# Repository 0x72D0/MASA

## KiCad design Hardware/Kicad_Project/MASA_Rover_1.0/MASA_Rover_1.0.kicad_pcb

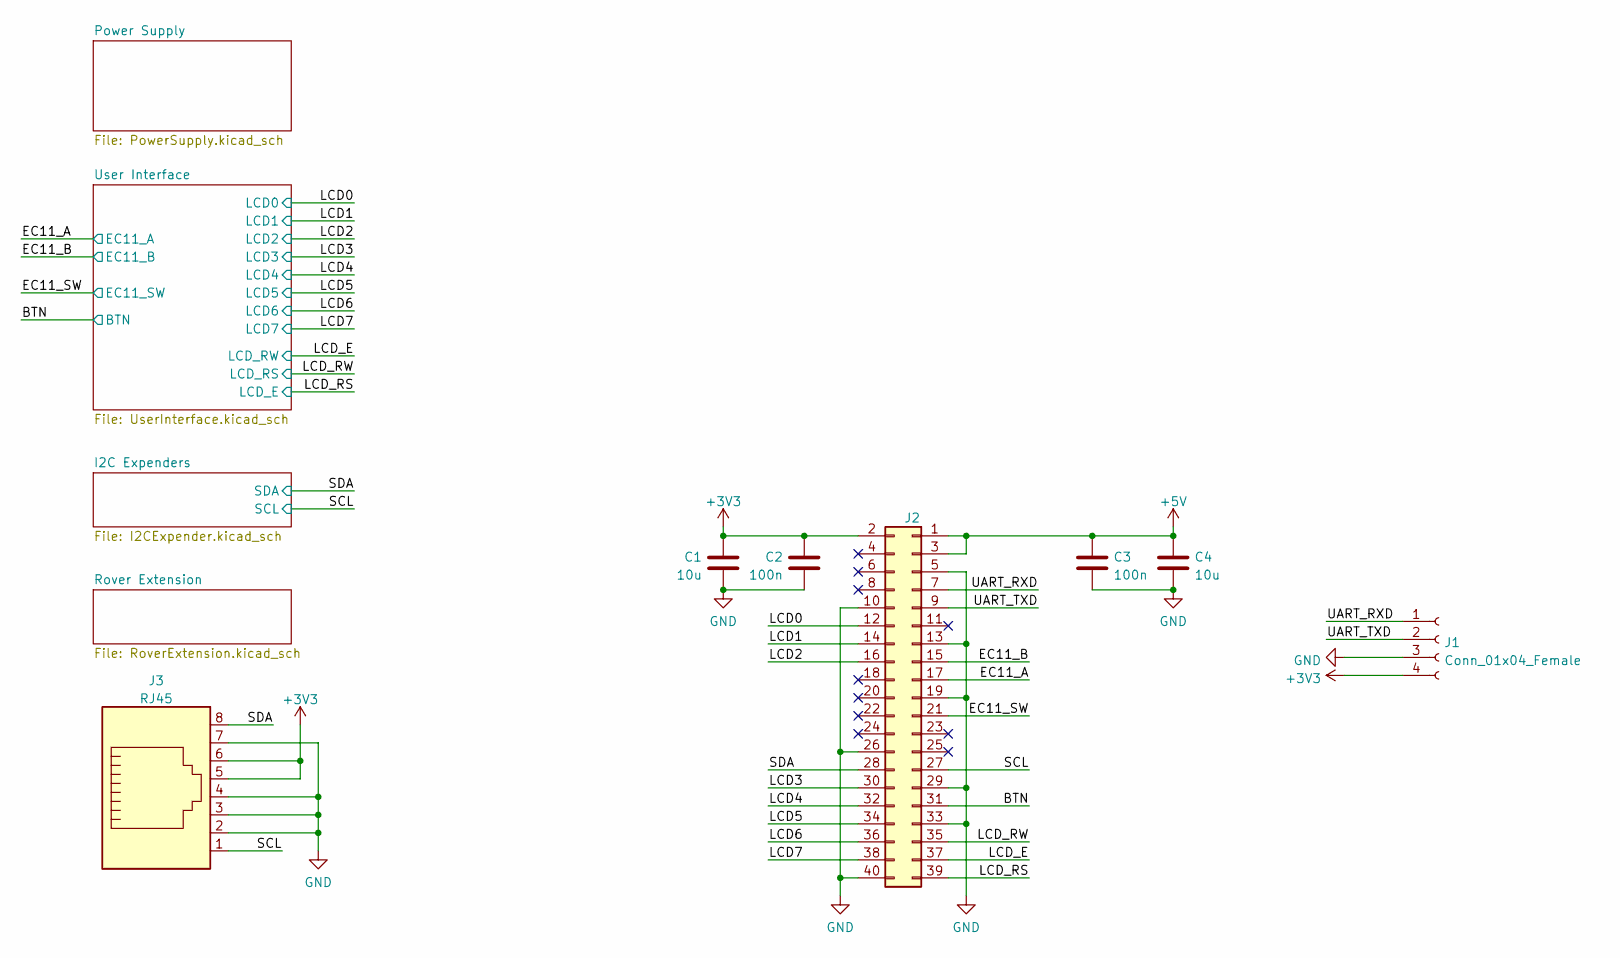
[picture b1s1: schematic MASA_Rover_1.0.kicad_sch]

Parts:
C1, C4: 10u; C_0805_2012Metric_Pad1.18x1.45mm_HandSolder
C2, C3: 100n; C_0805_2012Metric_Pad1.18x1.45mm_HandSolder
J1: Conn_01x04_Female; PinHeader_1x04_P2.54mm_Vertical
J2: Conn_02x20_Odd_Even; PinHeader_2x20_P2.54mm_Vertical
J3: RJ45; RJ45_Amphenol_54602-x08_Horizontal

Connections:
+3V3: C1.1, C2.1, J1.4, J2.2, J3.5, J3.6; also elsewhere on the board
+5V: C3.1, C4.1, J2.1, J2.3; also elsewhere on the board
/BTN: J2.31; also elsewhere on the board
/EC11_A: J2.17; also elsewhere on the board
/EC11_B: J2.15; also elsewhere on the board
/EC11_SW: J2.21; also elsewhere on the board
/LCD0: J2.12; also elsewhere on the board
/LCD1: J2.14; also elsewhere on the board
/LCD2: J2.16; also elsewhere on the board
/LCD3: J2.30; also elsewhere on the board
/LCD4: J2.32; also elsewhere on the board
/LCD5: J2.34; also elsewhere on the board
/LCD6: J2.36; also elsewhere on the board
/LCD7: J2.38; also elsewhere on the board
/LCD_E: J2.37; also elsewhere on the board
/LCD_RS: J2.39; also elsewhere on the board
/LCD_RW: J2.35; also elsewhere on the board
/SCL: J2.27, J3.1; also elsewhere on the board
/SDA: J2.28, J3.8; also elsewhere on the board
/UART_RXD: J1.1, J2.7
/UART_TXD: J1.2, J2.9
GND: C1.2, C2.2, C3.2, C4.2, J1.3, J2.5, J2.10, J2.13, J2.19, J2.26, J2.29, J2.33, J2.40, J3.2, J3.3, J3.4, J3.7; also elsewhere on the board

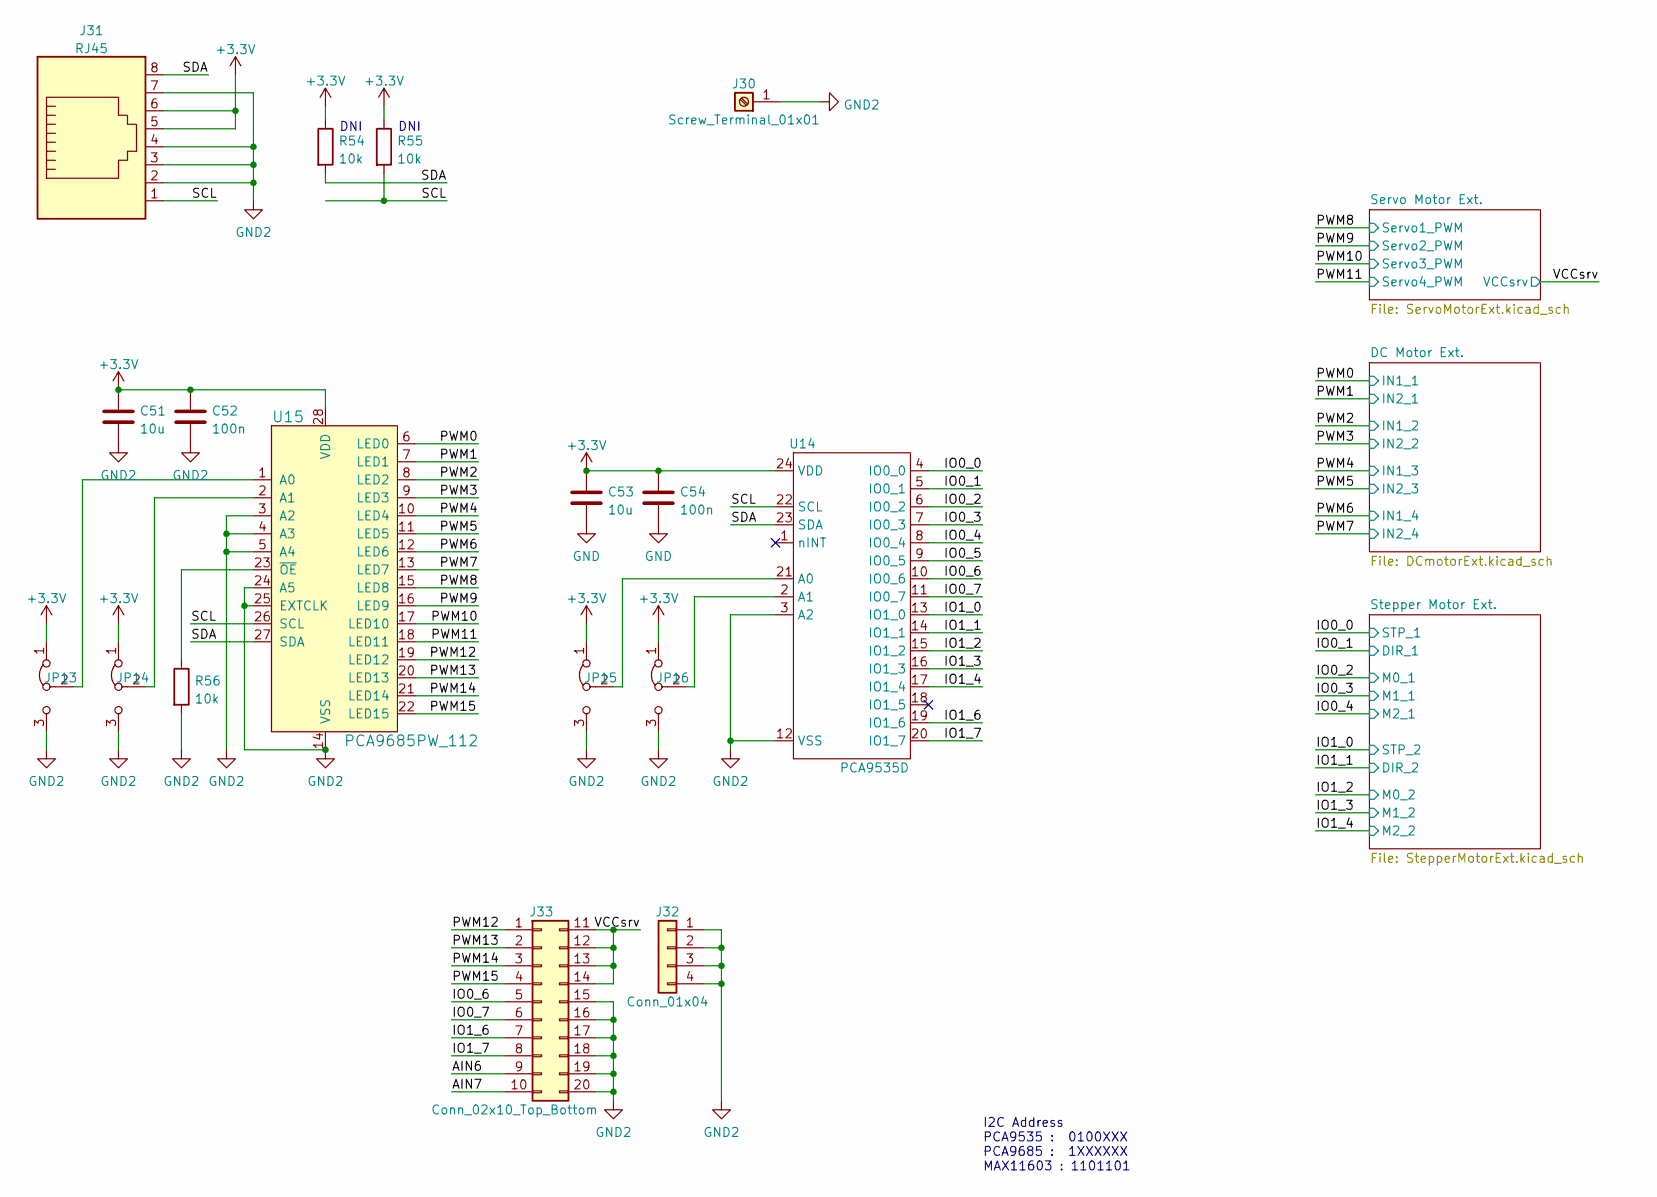
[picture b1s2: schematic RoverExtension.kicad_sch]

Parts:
C51, C53: 10u; C_0805_2012Metric_Pad1.18x1.45mm_HandSolder
C52, C54: 100n; C_0805_2012Metric_Pad1.18x1.45mm_HandSolder
J30: Screw_Terminal_01x01; ScrewTerminal_1x01_5x7mm
J31: RJ45; RJ45_Amphenol_54602-x08_Horizontal
J32: Conn_01x04; PinHeader_1x04_P2.54mm_Vertical
J33: Conn_02x10_Top_Bottom; PinHeader_2x10_P2.54mm_Vertical
JP13, JP14, JP15, JP16: Jumper_3_Bridged12; SolderJumper-3_P1.3mm_Bridged12_Pad1.0x1.5mm
R54, R55, R56: 10k; R_0805_2012Metric_Pad1.20x1.40mm_HandSolder
U14: PCA9535D; SOIC-24W_7.5x15.4mm_P1.27mm
U15: PCA9685PW_112; TSSOP-28_4.4x9.7mm_P0.65mm; MPN PCA9685PW,112; Digi-Key_PN 568-8366-5-ND

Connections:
+3.3V: C51.1, C52.1, C53.1, C54.1, J31.5, J31.6, JP13.1 (A), JP14.1 (A), JP15.1 (A), JP16.1 (A), R54.1, R55.1, U14.24 (VDD), U15.28 (VDD); also elsewhere on the board
/Rover Extension/AIN6: J33.9
/Rover Extension/AIN7: J33.10
/Rover Extension/IO0_0: U14.4 (IO0_0); also elsewhere on the board
/Rover Extension/IO0_1: U14.5 (IO0_1); also elsewhere on the board
/Rover Extension/IO0_2: U14.6 (IO0_2); also elsewhere on the board
/Rover Extension/IO0_3: U14.7 (IO0_3); also elsewhere on the board
/Rover Extension/IO0_4: U14.8 (IO0_4); also elsewhere on the board
/Rover Extension/IO0_5: U14.9 (IO0_5)
/Rover Extension/IO0_6: J33.5, U14.10 (IO0_6)
/Rover Extension/IO0_7: J33.6, U14.11 (IO0_7)
/Rover Extension/IO1_0: U14.13 (IO1_0); also elsewhere on the board
/Rover Extension/IO1_1: U14.14 (IO1_1); also elsewhere on the board
/Rover Extension/IO1_2: U14.15 (IO1_2); also elsewhere on the board
/Rover Extension/IO1_3: U14.16 (IO1_3); also elsewhere on the board
/Rover Extension/IO1_4: U14.17 (IO1_4); also elsewhere on the board
/Rover Extension/IO1_6: J33.7, U14.19 (IO1_6)
/Rover Extension/IO1_7: J33.8, U14.20 (IO1_7)
/Rover Extension/PWM0: U15.6 (LED0); also elsewhere on the board
/Rover Extension/PWM1: U15.7 (LED1); also elsewhere on the board
/Rover Extension/PWM2: U15.8 (LED2); also elsewhere on the board
/Rover Extension/PWM3: U15.9 (LED3); also elsewhere on the board
/Rover Extension/PWM4: U15.10 (LED4); also elsewhere on the board
/Rover Extension/PWM5: U15.11 (LED5); also elsewhere on the board
/Rover Extension/PWM6: U15.12 (LED6); also elsewhere on the board
/Rover Extension/PWM7: U15.13 (LED7); also elsewhere on the board
/Rover Extension/PWM8: U15.15 (LED8); also elsewhere on the board
/Rover Extension/PWM9: U15.16 (LED9); also elsewhere on the board
/Rover Extension/PWM10: U15.17 (LED10); also elsewhere on the board
/Rover Extension/PWM11: U15.18 (LED11); also elsewhere on the board
/Rover Extension/PWM12: J33.1, U15.19 (LED12)
/Rover Extension/PWM13: J33.2, U15.20 (LED13)
/Rover Extension/PWM14: J33.3, U15.21 (LED14)
/Rover Extension/PWM15: J33.4, U15.22 (LED15)
/Rover Extension/SCL: J31.1, R55.2, U14.22 (SCL), U15.26 (SCL)
/Rover Extension/SDA: J31.8, R54.2, U14.23 (SDA), U15.27 (SDA)
/Rover Extension/VCCsrv: J33.11, J33.12, J33.13, J33.14; also elsewhere on the board
GND: C53.2, C54.2; also elsewhere on the board
GND2: C51.2, C52.2, J30.1, J31.2, J31.3, J31.4, J31.7, J32.1, J32.2, J32.3, J32.4, J33.15, J33.16, J33.17, J33.18, J33.19, J33.20, JP13.3 (B), JP14.3 (B), JP15.3 (B), JP16.3 (B), R56.2, U14.3 (A2), U14.12 (VSS), U15.3 (A2), U15.4 (A3), U15.5 (A4), U15.14 (VSS), U15.24 (A5), U15.25 (EXTCLK); also elsewhere on the board
unnamed: JP13.2 (C), U15.1 (A0)
unnamed: JP14.2 (C), U15.2 (A1)
unnamed: JP15.2 (C), U14.21 (A0)
unnamed: JP16.2 (C), U14.2 (A1)
unnamed: R56.1, U15.23 (~OE)

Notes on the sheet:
DNI
I2C Address PCA9535 : 0100XXX PCA9685 : 1XXXXXX MAX11603 : 1101101

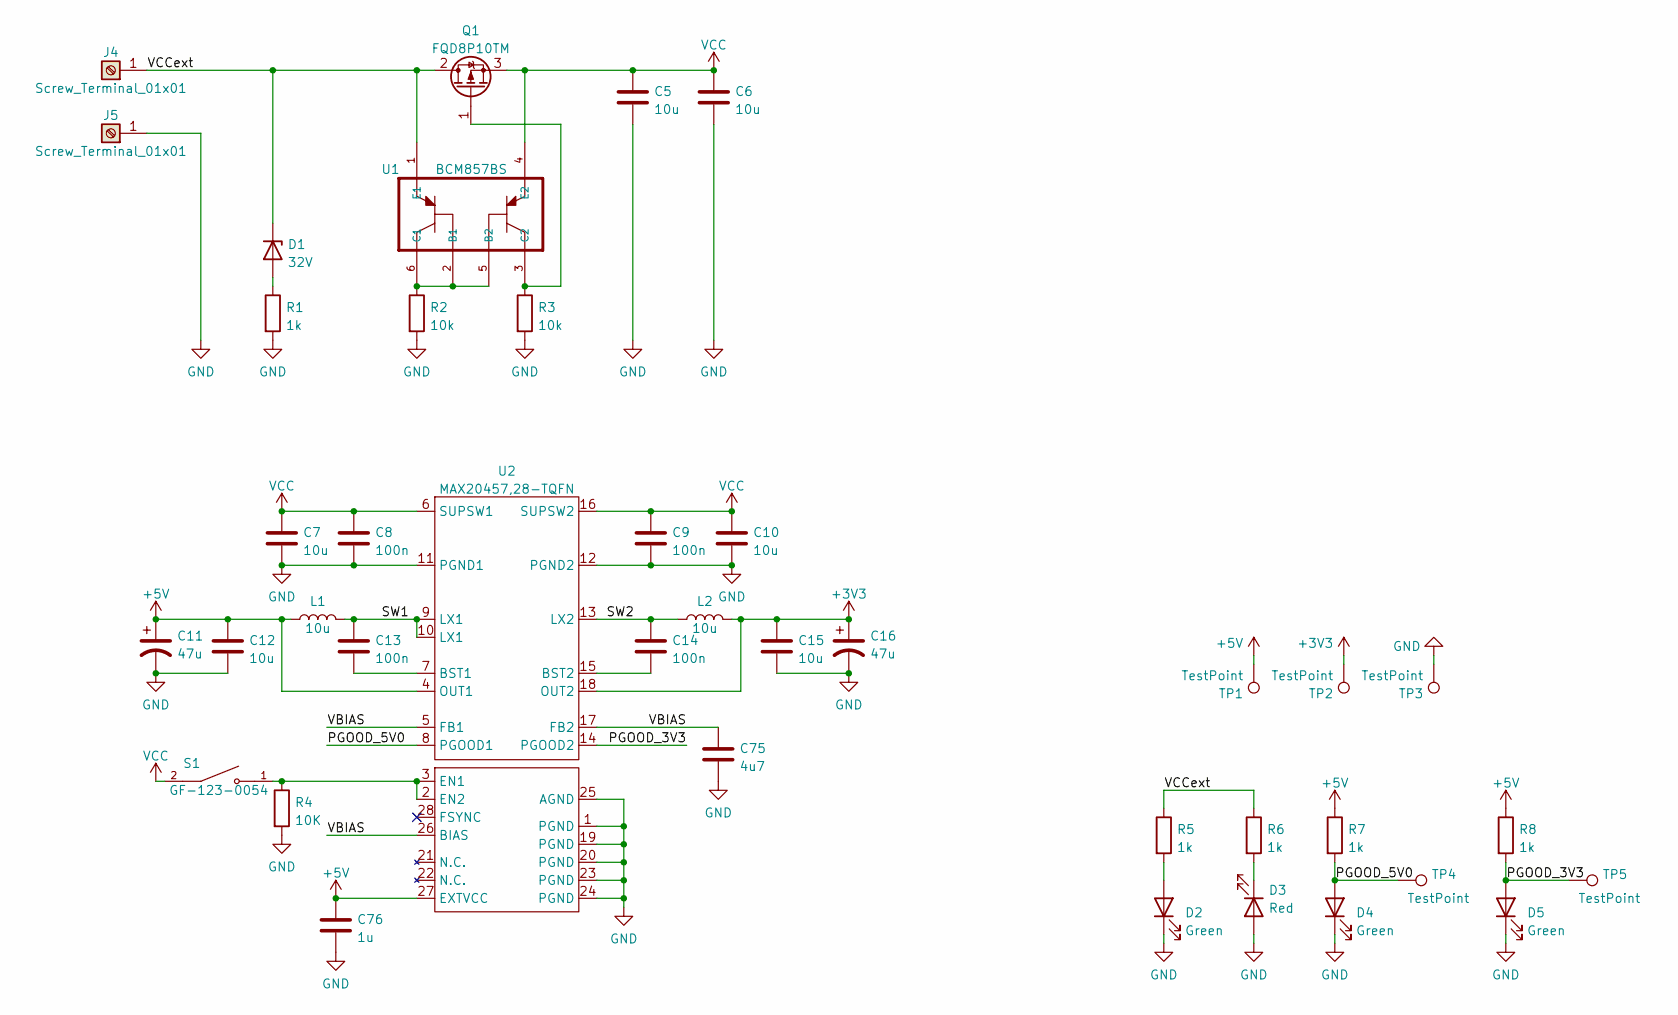
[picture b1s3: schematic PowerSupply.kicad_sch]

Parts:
C5, C6, C7, C10, C12, C15: 10u; C_0805_2012Metric_Pad1.18x1.45mm_HandSolder
C8, C9, C13, C14: 100n; C_0805_2012Metric_Pad1.18x1.45mm_HandSolder
C11, C16: 47u; C_Elec_6.3x5.8
C75: 4u7; C_0805_2012Metric_Pad1.18x1.45mm_HandSolder
C76: 1u; C_0805_2012Metric_Pad1.18x1.45mm_HandSolder
D1: 32V; C_0805_2012Metric_Pad1.18x1.45mm_HandSolder
D2, D4, D5: Green; D_0805_2012Metric_Pad1.15x1.40mm_HandSolder
D3: Red; D_0805_2012Metric_Pad1.15x1.40mm_HandSolder
J4, J5: Screw_Terminal_01x01; ScrewTerminal_1x01_5x7mm
L1: 10u; L_10.7x10.0mm_H4mm
L2: 10u; L_1210_3225Metric_Pad1.42x2.65mm_HandSolder
Q1: FQD8P10TM; TO-252-2
R1, R5, R6, R7, R8: 1k; R_0805_2012Metric_Pad1.20x1.40mm_HandSolder
R2, R3: 10k; R_0805_2012Metric_Pad1.20x1.40mm_HandSolder
R4: 10K; R_0805_2012Metric_Pad1.20x1.40mm_HandSolder
S1: GF-123-0054; SW_GF-123-0054; PARTREV May 20, 2003
TP1, TP2, TP3, TP4, TP5: TestPoint; TestPoint_Pad_D2.0mm
U1: BCM857BS; SOT-363_SC-70-6_Handsoldering
U2: MAX20457,28-TQFN; TQFN-28-1EP_5x5mm_P0.5mm_EP2.7x2.7mm

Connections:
+3V3: C15.1, C16.1, L2.2, TP2.1, U2.18 (OUT2); also elsewhere on the board
+5V: C11.1, C12.1, C76.1, L1.1, R7.1, R8.1, TP1.1, U2.4 (OUT1), U2.27 (EXTVCC); also elsewhere on the board
/Power Supply/PGOOD_3V3: D5.2 (A), R8.2, TP5.1, U2.14 (PGOOD2)
/Power Supply/PGOOD_5V0: D4.2 (A), R7.2, TP4.1, U2.8 (PGOOD1)
/Power Supply/SW1: C13.2, L1.2, U2.9 (LX1), U2.10 (LX1)
/Power Supply/SW2: C14.2, L2.1, U2.13 (LX2)
/Power Supply/VBIAS: C75.1, U2.5 (FB1), U2.17 (FB2), U2.26 (BIAS)
/Power Supply/VCCext: D1.1 (K), J4.1, Q1.2 (D), R5.1, R6.1, U1.1 (E1)
GND: C5.2, C6.2, C7.2, C8.2, C9.2, C10.2, C11.2, C12.2, C15.2, C16.2, C75.2, C76.2, D2.1 (K), D3.2 (A), D4.1 (K), D5.1 (K), J5.1, R1.2, R2.2, R3.2, R4.2, TP3.1, U2.1 (PGND), U2.11 (PGND1), U2.12 (PGND2), U2.19 (PGND), U2.20 (PGND), U2.23 (PGND), U2.24 (PGND), U2.25 (AGND); also elsewhere on the board
unnamed: C13.1, U2.7 (BST1)
unnamed: C14.1, U2.15 (BST2)
unnamed: D1.2 (A), R1.1
unnamed: D2.2 (A), R5.2
unnamed: D3.1 (K), R6.2
unnamed: Q1.1 (G), R3.1, U1.3 (C2)
unnamed: R2.1, U1.2 (B1), U1.5 (B2), U1.6 (C1)
unnamed: R4.1, S1.1, U2.2 (EN2), U2.3 (EN1)
VCC: C5.1, C6.1, C7.1, C8.1, C9.1, C10.1, Q1.3 (S), S1.2, U1.4 (E2), U2.6 (SUPSW1), U2.16 (SUPSW2)

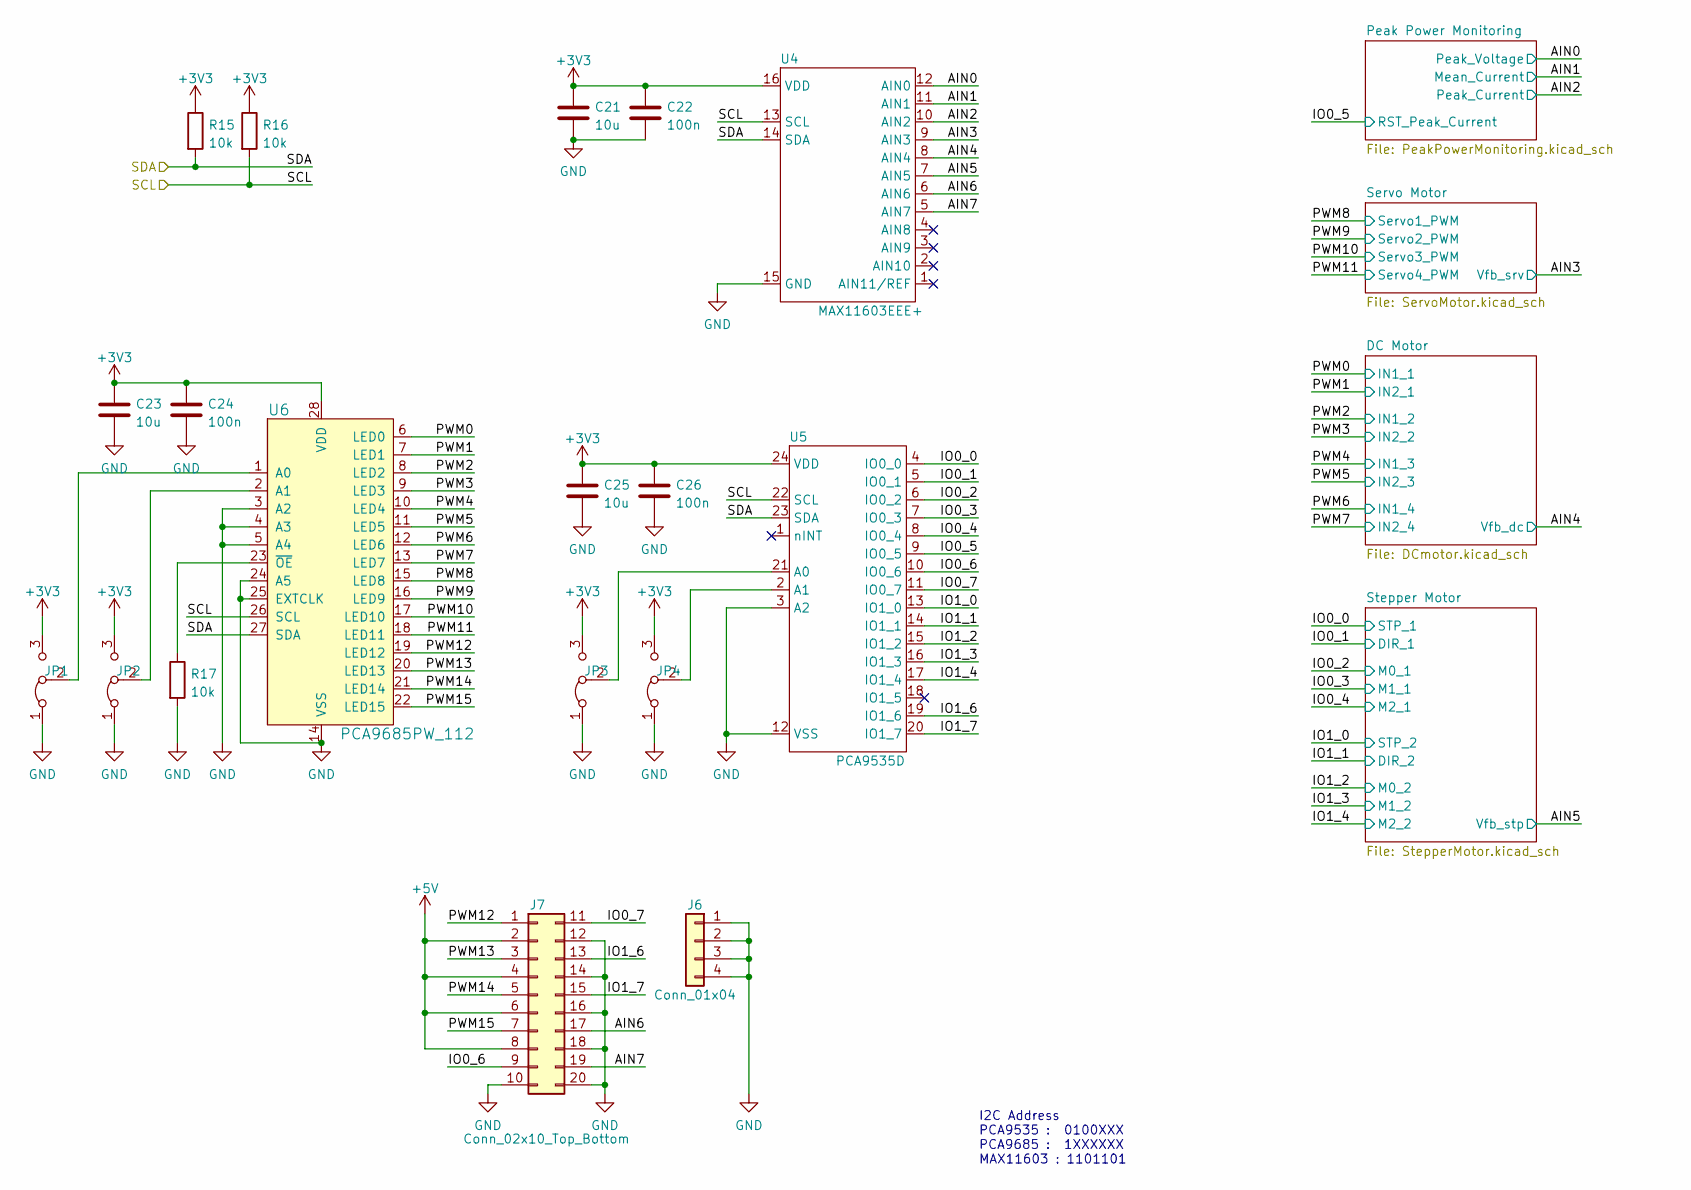
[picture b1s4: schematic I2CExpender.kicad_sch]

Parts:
C21, C23, C25: 10u; C_0805_2012Metric_Pad1.18x1.45mm_HandSolder
C22, C24, C26: 100n; C_0805_2012Metric_Pad1.18x1.45mm_HandSolder
J6: Conn_01x04; PinHeader_1x04_P2.54mm_Vertical
J7: Conn_02x10_Top_Bottom; PinHeader_2x10_P2.54mm_Vertical
JP1, JP2, JP3, JP4: Jumper_3_Bridged12; SolderJumper-3_P1.3mm_Bridged12_Pad1.0x1.5mm
R15, R16, R17: 10k; R_0805_2012Metric_Pad1.20x1.40mm_HandSolder
U4: MAX11603EEE+; SSOP-16_3.9x4.9mm_P0.635mm
U5: PCA9535D; SOIC-24W_7.5x15.4mm_P1.27mm
U6: PCA9685PW_112; TSSOP-28_4.4x9.7mm_P0.65mm; MPN PCA9685PW,112; Digi-Key_PN 568-8366-5-ND

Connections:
+3V3: C21.1, C22.1, C23.1, C24.1, C25.1, C26.1, JP1.3 (B), JP2.3 (B), JP3.3 (B), JP4.3 (B), R15.1, R16.1, U4.16 (VDD), U5.24 (VDD), U6.28 (VDD); also elsewhere on the board
+5V: J7.2, J7.4, J7.6, J7.8; also elsewhere on the board
/I2C Expenders/AIN0: U4.12 (AIN0); also elsewhere on the board
/I2C Expenders/AIN1: U4.11 (AIN1); also elsewhere on the board
/I2C Expenders/AIN2: U4.10 (AIN2); also elsewhere on the board
/I2C Expenders/AIN3: U4.9 (AIN3); also elsewhere on the board
/I2C Expenders/AIN4: U4.8 (AIN4); also elsewhere on the board
/I2C Expenders/AIN5: U4.7 (AIN5); also elsewhere on the board
/I2C Expenders/AIN6: J7.17, U4.6 (AIN6)
/I2C Expenders/AIN7: J7.19, U4.5 (AIN7)
/I2C Expenders/IO0_0: U5.4 (IO0_0); also elsewhere on the board
/I2C Expenders/IO0_1: U5.5 (IO0_1); also elsewhere on the board
/I2C Expenders/IO0_2: U5.6 (IO0_2); also elsewhere on the board
/I2C Expenders/IO0_3: U5.7 (IO0_3); also elsewhere on the board
/I2C Expenders/IO0_4: U5.8 (IO0_4); also elsewhere on the board
/I2C Expenders/IO0_5: U5.9 (IO0_5); also elsewhere on the board
/I2C Expenders/IO0_6: J7.9, U5.10 (IO0_6)
/I2C Expenders/IO0_7: J7.11, U5.11 (IO0_7)
/I2C Expenders/IO1_0: U5.13 (IO1_0); also elsewhere on the board
/I2C Expenders/IO1_1: U5.14 (IO1_1); also elsewhere on the board
/I2C Expenders/IO1_2: U5.15 (IO1_2); also elsewhere on the board
/I2C Expenders/IO1_3: U5.16 (IO1_3); also elsewhere on the board
/I2C Expenders/IO1_4: U5.17 (IO1_4); also elsewhere on the board
/I2C Expenders/IO1_6: J7.13, U5.19 (IO1_6)
/I2C Expenders/IO1_7: J7.15, U5.20 (IO1_7)
/I2C Expenders/PWM0: U6.6 (LED0); also elsewhere on the board
/I2C Expenders/PWM1: U6.7 (LED1); also elsewhere on the board
/I2C Expenders/PWM2: U6.8 (LED2); also elsewhere on the board
/I2C Expenders/PWM3: U6.9 (LED3); also elsewhere on the board
/I2C Expenders/PWM4: U6.10 (LED4); also elsewhere on the board
/I2C Expenders/PWM5: U6.11 (LED5); also elsewhere on the board
/I2C Expenders/PWM6: U6.12 (LED6); also elsewhere on the board
/I2C Expenders/PWM7: U6.13 (LED7); also elsewhere on the board
/I2C Expenders/PWM8: U6.15 (LED8); also elsewhere on the board
/I2C Expenders/PWM9: U6.16 (LED9); also elsewhere on the board
/I2C Expenders/PWM10: U6.17 (LED10); also elsewhere on the board
/I2C Expenders/PWM11: U6.18 (LED11); also elsewhere on the board
/I2C Expenders/PWM12: J7.1, U6.19 (LED12)
/I2C Expenders/PWM13: J7.3, U6.20 (LED13)
/I2C Expenders/PWM14: J7.5, U6.21 (LED14)
/I2C Expenders/PWM15: J7.7, U6.22 (LED15)
/SCL: R16.2, U4.13 (SCL), U5.22 (SCL), U6.26 (SCL); also elsewhere on the board
/SDA: R15.2, U4.14 (SDA), U5.23 (SDA), U6.27 (SDA); also elsewhere on the board
GND: C21.2, C22.2, C23.2, C24.2, C25.2, C26.2, J6.1, J6.2, J6.3, J6.4, J7.10, J7.12, J7.14, J7.16, J7.18, J7.20, JP1.1 (A), JP2.1 (A), JP3.1 (A), JP4.1 (A), R17.2, U4.15 (GND), U5.3 (A2), U5.12 (VSS), U6.3 (A2), U6.4 (A3), U6.5 (A4), U6.14 (VSS), U6.24 (A5), U6.25 (EXTCLK); also elsewhere on the board
unnamed: JP1.2 (C), U6.1 (A0)
unnamed: JP2.2 (C), U6.2 (A1)
unnamed: JP3.2 (C), U5.21 (A0)
unnamed: JP4.2 (C), U5.2 (A1)
unnamed: R17.1, U6.23 (~OE)

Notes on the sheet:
I2C Address PCA9535 : 0100XXX PCA9685 : 1XXXXXX MAX11603 : 1101101

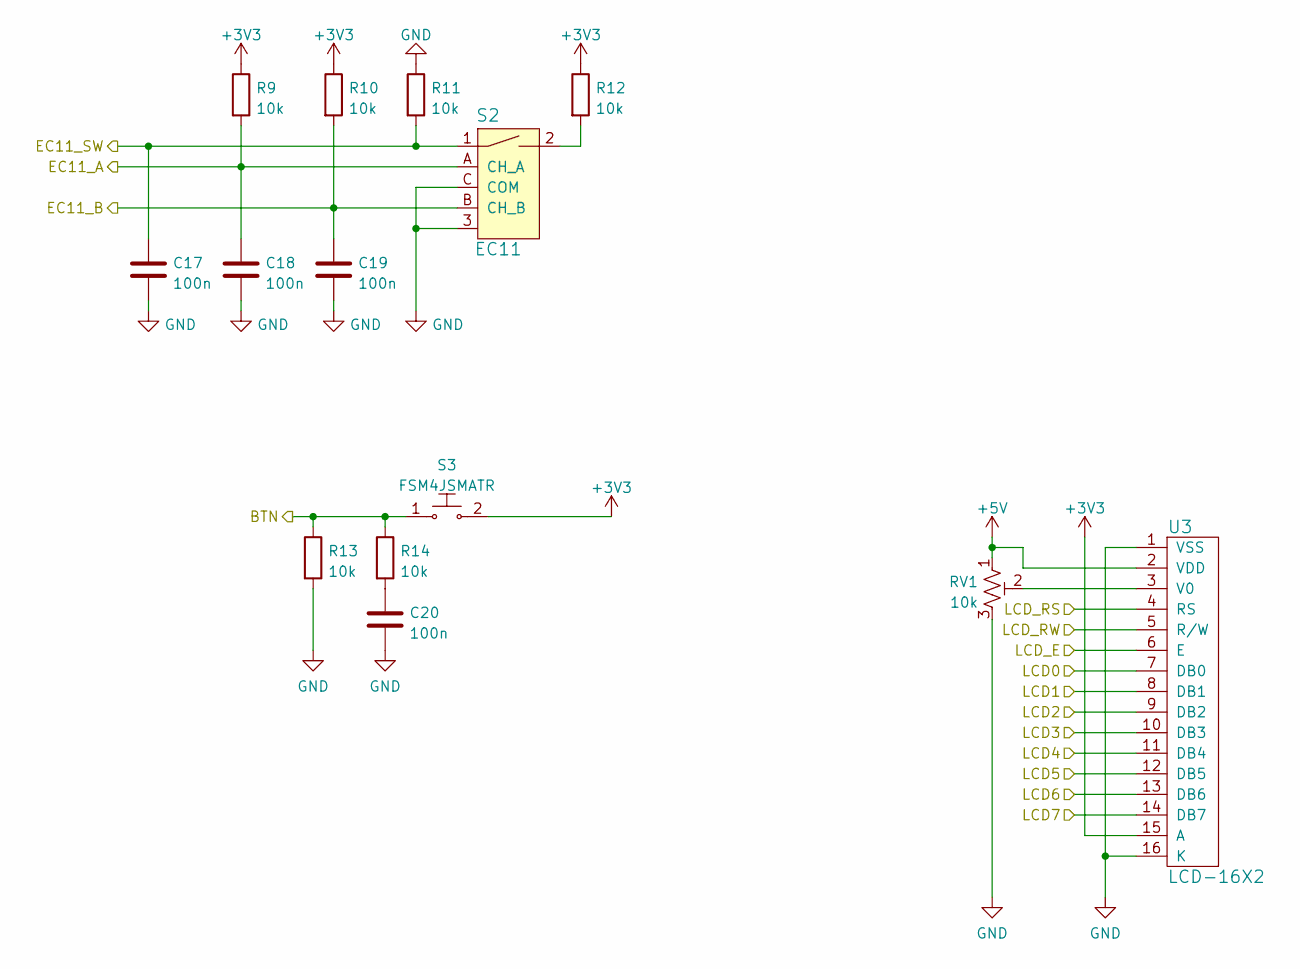
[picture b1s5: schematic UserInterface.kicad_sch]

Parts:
C17, C18, C19, C20: 100n; C_0805_2012Metric_Pad1.18x1.45mm_HandSolder
R9, R10, R11, R12, R13, R14: 10k; R_0805_2012Metric_Pad1.20x1.40mm_HandSolder
RV1: 10k; Potentiometer_Bourns_3296X_Horizontal
S2: EC11; EC11E; MPN PEC11R-4215F-S0024; Digi-Key_PN PEC11R-4215F-S0024-ND
S3: FSM4JSMATR; SW_Push_1P1T_NO_6x6mm_H9.5mm; MPN FSM4JSMATR
U3: LCD-16X2; WC1602A

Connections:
+3V3: R9.1, R10.1, R12.1, S3.2, U3.15 (A); also elsewhere on the board
+5V: RV1.1, U3.2 (VDD); also elsewhere on the board
/BTN: R13.1, R14.1, S3.1; also elsewhere on the board
/EC11_A: C18.1, R9.2, S2.A (CH_A); also elsewhere on the board
/EC11_B: C19.1, R10.2, S2.B (CH_B); also elsewhere on the board
/EC11_SW: C17.1, R11.2, S2.1; also elsewhere on the board
/LCD0: U3.7 (DB0); also elsewhere on the board
/LCD1: U3.8 (DB1); also elsewhere on the board
/LCD2: U3.9 (DB2); also elsewhere on the board
/LCD3: U3.10 (DB3); also elsewhere on the board
/LCD4: U3.11 (DB4); also elsewhere on the board
/LCD5: U3.12 (DB5); also elsewhere on the board
/LCD6: U3.13 (DB6); also elsewhere on the board
/LCD7: U3.14 (DB7); also elsewhere on the board
/LCD_E: U3.5 (R/W); also elsewhere on the board
/LCD_RS: U3.6 (E); also elsewhere on the board
/LCD_RW: U3.4 (RS); also elsewhere on the board
GND: C17.2, C18.2, C19.2, C20.2, R11.1, R13.2, RV1.3, S2.3, S2.C (COM), U3.1 (VSS), U3.16 (K); also elsewhere on the board
unnamed: C20.1, R14.2
unnamed: R12.2, S2.2
unnamed: RV1.2, U3.3 (V0)

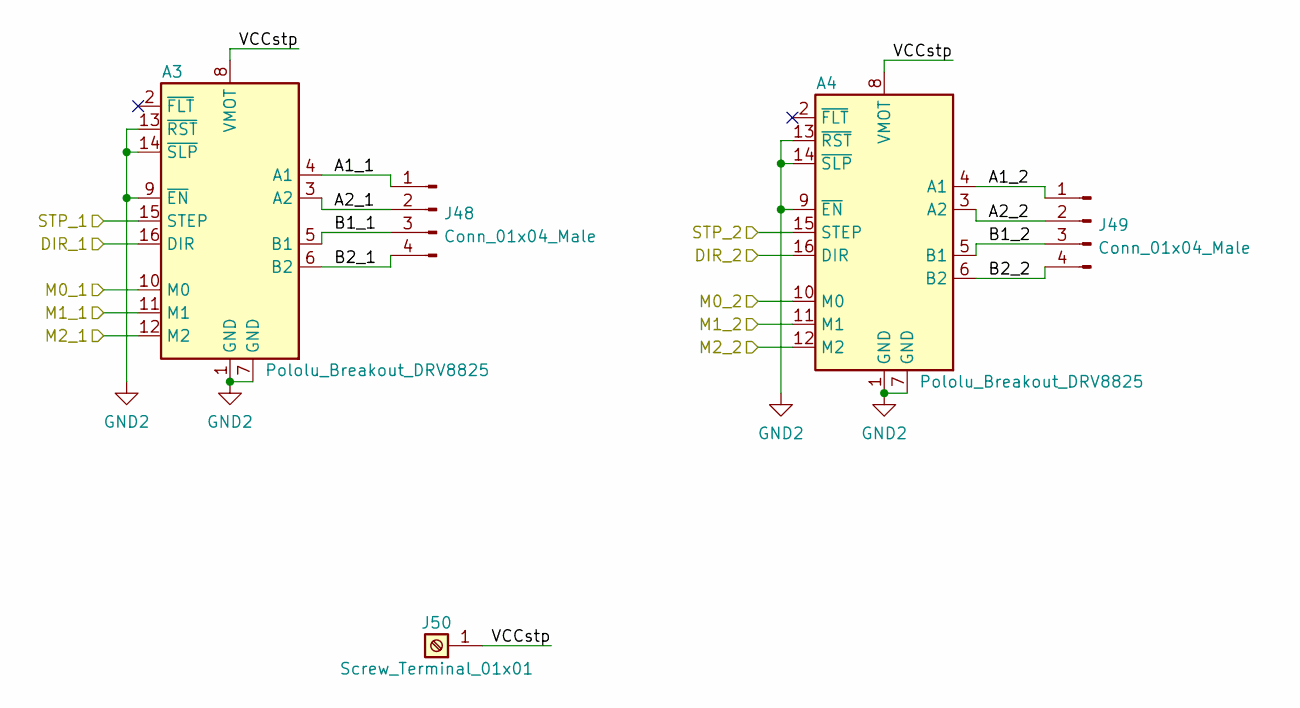
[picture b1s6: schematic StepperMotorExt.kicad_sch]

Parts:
A3, A4: Pololu_Breakout_DRV8825; Pololu_Breakout-16_15.2x20.3mm
J48, J49: Conn_01x04_Male; PinHeader_1x04_P2.54mm_Vertical
J50: Screw_Terminal_01x01; ScrewTerminal_1x01_5x7mm

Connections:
/Rover Extension/IO0_0: A3.15 (STEP); also elsewhere on the board
/Rover Extension/IO0_1: A3.16 (DIR); also elsewhere on the board
/Rover Extension/IO0_2: A3.10 (M0); also elsewhere on the board
/Rover Extension/IO0_3: A3.11 (M1); also elsewhere on the board
/Rover Extension/IO0_4: A3.12 (M2); also elsewhere on the board
/Rover Extension/IO1_0: A4.15 (STEP); also elsewhere on the board
/Rover Extension/IO1_1: A4.16 (DIR); also elsewhere on the board
/Rover Extension/IO1_2: A4.10 (M0); also elsewhere on the board
/Rover Extension/IO1_3: A4.11 (M1); also elsewhere on the board
/Rover Extension/IO1_4: A4.12 (M2); also elsewhere on the board
/Rover Extension/Stepper Motor Ext./A1_1: A3.4 (A1), J48.1
/Rover Extension/Stepper Motor Ext./A1_2: A4.4 (A1), J49.1
/Rover Extension/Stepper Motor Ext./A2_1: A3.3 (A2), J48.2
/Rover Extension/Stepper Motor Ext./A2_2: A4.3 (A2), J49.2
/Rover Extension/Stepper Motor Ext./B1_1: A3.5 (B1), J48.3
/Rover Extension/Stepper Motor Ext./B1_2: A4.5 (B1), J49.3
/Rover Extension/Stepper Motor Ext./B2_1: A3.6 (B2), J48.4
/Rover Extension/Stepper Motor Ext./B2_2: A4.6 (B2), J49.4
/Rover Extension/Stepper Motor Ext./VCCstp: A3.8 (VMOT), A4.8 (VMOT), J50.1
GND2: A3.1 (GND), A3.7 (GND), A3.9 (~EN), A3.13 (~RST), A3.14 (~SLP), A4.1 (GND), A4.7 (GND), A4.9 (~EN), A4.13 (~RST), A4.14 (~SLP); also elsewhere on the board

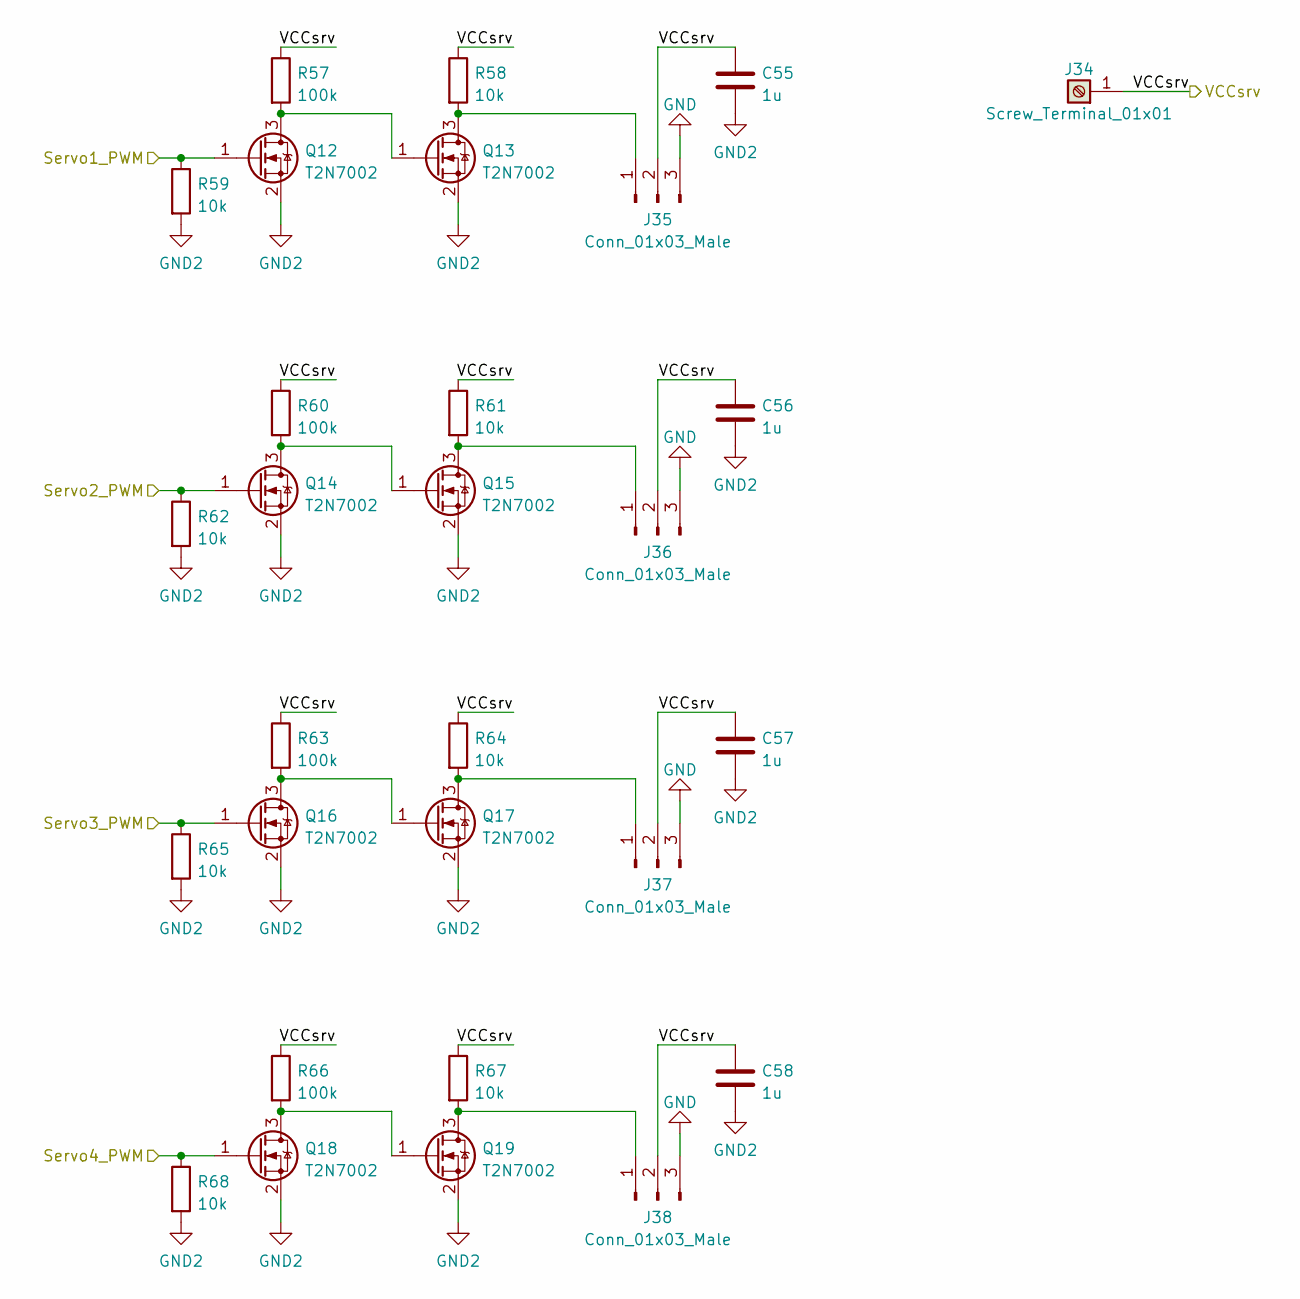
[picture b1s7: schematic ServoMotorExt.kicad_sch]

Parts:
C55, C56, C57, C58: 1u; C_0805_2012Metric_Pad1.18x1.45mm_HandSolder
J34: Screw_Terminal_01x01; ScrewTerminal_1x01_5x7mm
J35, J36, J37, J38: Conn_01x03_Male; PinHeader_1x03_P2.54mm_Vertical
Q12, Q13, Q14, Q15, Q16, Q17, Q18, Q19: T2N7002; SOT-23
R57, R60, R63, R66: 100k; R_0805_2012Metric_Pad1.20x1.40mm_HandSolder
R58, R59, R61, R62, R64, R65, R67, R68: 10k; R_0805_2012Metric_Pad1.20x1.40mm_HandSolder

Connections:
/Rover Extension/PWM8: Q12.1 (G), R59.1; also elsewhere on the board
/Rover Extension/PWM9: Q14.1 (G), R62.1; also elsewhere on the board
/Rover Extension/PWM10: Q16.1 (G), R65.1; also elsewhere on the board
/Rover Extension/PWM11: Q18.1 (G), R68.1; also elsewhere on the board
/Rover Extension/VCCsrv: C55.1, C56.1, C57.1, C58.1, J34.1, J35.2, J36.2, J37.2, J38.2, R57.1, R58.1, R60.1, R61.1, R63.1, R64.1, R66.1, R67.1; also elsewhere on the board
GND: J35.3, J36.3, J37.3, J38.3; also elsewhere on the board
GND2: C55.2, C56.2, C57.2, C58.2, Q12.2 (S), Q13.2 (S), Q14.2 (S), Q15.2 (S), Q16.2 (S), Q17.2 (S), Q18.2 (S), Q19.2 (S), R59.2, R62.2, R65.2, R68.2; also elsewhere on the board
unnamed: J35.1, Q13.3 (D), R58.2
unnamed: J36.1, Q15.3 (D), R61.2
unnamed: J37.1, Q17.3 (D), R64.2
unnamed: J38.1, Q19.3 (D), R67.2
unnamed: Q12.3 (D), Q13.1 (G), R57.2
unnamed: Q14.3 (D), Q15.1 (G), R60.2
unnamed: Q16.3 (D), Q17.1 (G), R63.2
unnamed: Q18.3 (D), Q19.1 (G), R66.2
